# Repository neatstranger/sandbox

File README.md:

## Purpose
Just needed a place to document the build.

## Overview
- Clock
- Registers
- Arithmetic Logic unit
- Random Access Memory
- Program Counter
- Output Register

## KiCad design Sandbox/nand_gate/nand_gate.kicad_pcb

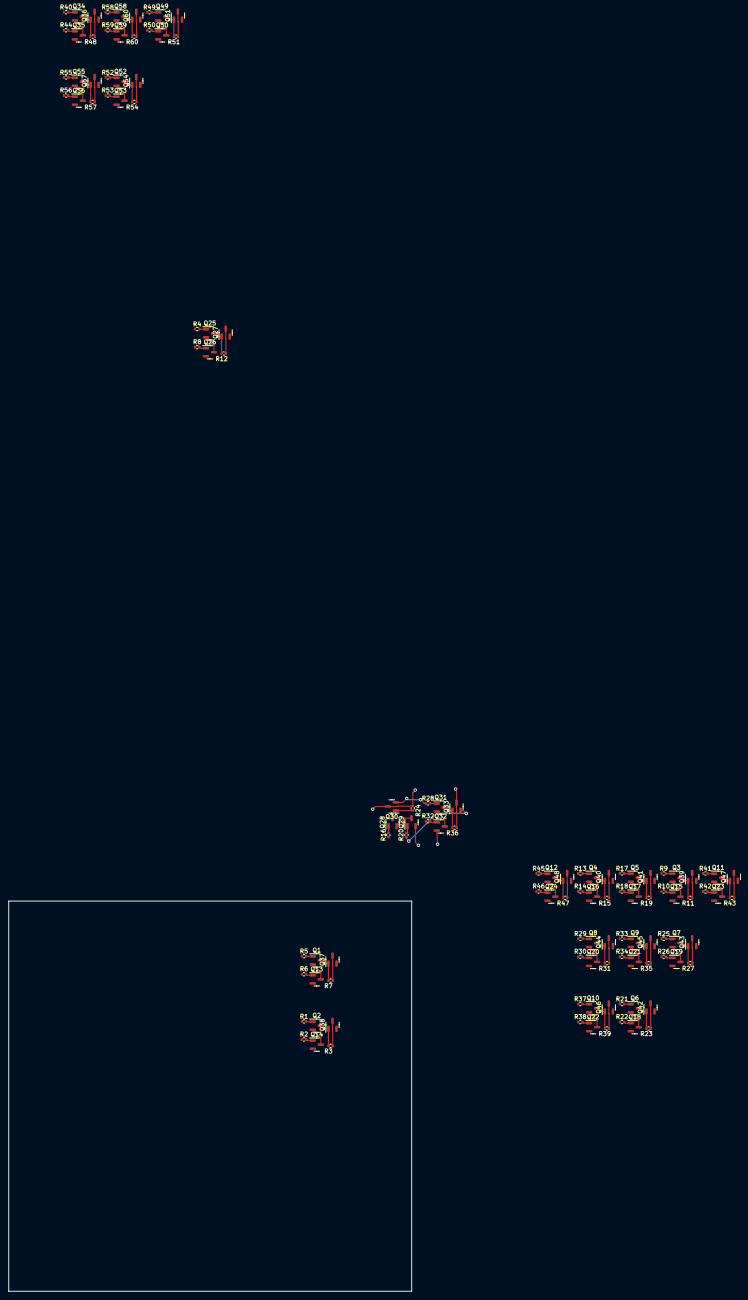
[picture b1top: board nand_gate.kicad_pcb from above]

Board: 4 copper layers, 94.8 x 91.8 mm, 120 parts (0 on the bottom side), 105 nets.

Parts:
Q1, Q2, Q3, Q4, Q5, Q6, Q7, Q8, Q9, Q10, Q11, Q12, Q13, Q14, Q15, Q16, Q17, Q18, Q19, Q20, Q21, Q22, Q23, Q24, Q25, Q26, Q27, Q28, Q29, Q30, Q31, Q32, Q33, Q34, Q35, Q36, Q37, Q38, Q39, Q40, Q41, Q42, Q43, Q44, Q45, Q46, Q47, Q48, Q49, Q50, Q51, Q52, Q53, Q54, Q55, Q56, Q57, Q58, Q59, Q60: Q_NPN_BEC; SOT-23
R1, R2, R3, R4, R5, R6, R7, R8, R9, R10, R11, R12, R13, R14, R15, R16, R17, R18, R19, R20, R21, R22, R23, R24, R25, R26, R27, R28, R29, R30, R31, R32, R33, R34, R35, R36, R37, R38, R39, R40, R41, R42, R43, R44, R45, R46, R47, R48, R49, R50, R51, R52, R53, R54, R55, R56, R57, R58, R59, R60: 1k; R_0402_1005Metric

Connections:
/D-Flip Flop/!Q: Q46.2 (E), R30.1
/D-Flip Flop/Clock: R41.1, R42.1
/D-Flip Flop/D-Latch1/Enable: Q48.2 (E), R26.1, R33.1
/D-Flip Flop/D-Latch1/SR-Latch/Reset: Q45.2 (E), R38.1
/D-Flip Flop/D-Latch1/SR-Latch/Set: Q43.2 (E), R29.1
/D-Flip Flop/D-Latch1/nand_gate3/B: Q42.2 (E), R34.1
/D-Flip Flop/D-Latch/!Q: Q38.2 (E), R6.1
/D-Flip Flop/D-Latch/Enable: Q47.2 (E), R10.1, R13.1, R45.1, R46.1
/D-Flip Flop/D-Latch/Q: Q37.2 (E), R1.1, R21.1, R22.1, R25.1
/D-Flip Flop/D-Latch/SR-Latch/Reset: Q40.2 (E), R2.1
/D-Flip Flop/D-Latch/SR-Latch/Set: Q39.2 (E), R5.1
/D-Flip Flop/D-Latch/nand_gate3/B: Q41.2 (E), R14.1
/D-Flip Flop/Data: R9.1, R17.1, R18.1
/D-Flip Flop/Q: Q44.2 (E), R37.1
/D-Latch2/!Q: Q57.2 (E), R44.1
/D-Latch2/Data: R49.1, R50.1, R52.1
/D-Latch2/Enable: R53.1, R58.1
/D-Latch2/Q: Q36.2 (E), R55.1
/D-Latch2/SR-Latch/Reset: Q60.2 (E), R56.1
/D-Latch2/SR-Latch/Set: Q54.2 (E), R40.1
/D-Latch2/nand_gate3/B: Q51.2 (E), R59.1
/SR-Latch1/!Q: Q33.2 (E), R20.1
/SR-Latch1/Q: Q30.2 (E), R28.1
GND: Q13.2 (E), Q14.2 (E), Q15.2 (E), Q16.2 (E), Q17.2 (E), Q18.2 (E), Q19.2 (E), Q20.2 (E), Q21.2 (E), Q22.2 (E), Q23.2 (E), Q24.2 (E), Q26.2 (E), Q29.2 (E), Q32.2 (E), Q35.2 (E), Q50.2 (E), Q53.2 (E), Q56.2 (E), Q59.2 (E)
unnamed: Q1.1 (B), R5.2
unnamed: Q1.3 (C), Q37.1 (B), R7.1
unnamed: Q1.2 (E), Q13.3 (C)
unnamed: Q2.1 (B), R1.2
unnamed: Q2.3 (C), Q38.1 (B), R3.1
unnamed: Q3.1 (B), R9.2
unnamed: Q3.3 (C), Q39.1 (B), R11.1
unnamed: Q4.1 (B), R13.2
unnamed: Q4.3 (C), Q40.1 (B), R15.1
unnamed: Q5.1 (B), R17.2
unnamed: Q6.1 (B), R21.2
unnamed: Q7.1 (B), R25.2
unnamed: Q8.1 (B), R29.2
unnamed: Q9.1 (B), R33.2
unnamed: Q10.1 (B), R37.2
unnamed: Q10.3 (C), Q46.1 (B), R39.1
unnamed: Q10.2 (E), Q22.3 (C)
unnamed: Q11.1 (B), R41.2
unnamed: Q11.3 (C), Q47.1 (B), R43.1
unnamed: Q11.2 (E), Q23.3 (C)
unnamed: Q12.1 (B), R45.2
unnamed: Q12.3 (C), Q48.1 (B), R47.1
unnamed: Q12.2 (E), Q24.3 (C)
unnamed: Q13.1 (B), R6.2
unnamed: Q14.1 (B), R2.2
unnamed: Q2.2 (E), Q14.3 (C)
unnamed: Q15.1 (B), R10.2
unnamed: Q3.2 (E), Q15.3 (C)
unnamed: Q16.1 (B), R14.2
unnamed: Q4.2 (E), Q16.3 (C)
unnamed: Q17.1 (B), R18.2
unnamed: Q5.2 (E), Q17.3 (C)
unnamed: Q18.1 (B), R22.2
unnamed: Q6.2 (E), Q18.3 (C)
unnamed: Q19.1 (B), R26.2
unnamed: Q7.2 (E), Q19.3 (C)
unnamed: Q20.1 (B), R30.2
unnamed: Q8.2 (E), Q20.3 (C)
unnamed: Q21.1 (B), R34.2
unnamed: Q9.2 (E), Q21.3 (C)
unnamed: Q22.1 (B), R38.2
unnamed: Q23.1 (B), R42.2
unnamed: Q24.1 (B), R46.2
unnamed: Q25.1 (B), R4.2
unnamed: Q25.3 (C), Q27.1 (B), R12.1
unnamed: Q25.2 (E), Q26.3 (C)
unnamed: Q26.1 (B), R8.2
unnamed: Q28.1 (B), R16.2
unnamed: Q28.3 (C), Q30.1 (B), R24.1
unnamed: Q28.2 (E), Q29.3 (C)
unnamed: Q29.1 (B), R20.2
unnamed: Q31.1 (B), R28.2
unnamed: Q31.3 (C), Q33.1 (B), R36.1
unnamed: Q31.2 (E), Q32.3 (C)
unnamed: Q32.1 (B), R32.2
unnamed: Q34.1 (B), R40.2
unnamed: Q34.3 (C), Q36.1 (B), R48.1
unnamed: Q34.2 (E), Q35.3 (C)
unnamed: Q35.1 (B), R44.2
unnamed: Q5.3 (C), Q41.1 (B), R19.1
unnamed: Q6.3 (C), Q42.1 (B), R23.1
unnamed: Q7.3 (C), Q43.1 (B), R27.1
unnamed: Q8.3 (C), Q44.1 (B), R31.1
unnamed: Q9.3 (C), Q45.1 (B), R35.1
unnamed: Q49.1 (B), R49.2
unnamed: Q49.3 (C), Q51.1 (B), R51.1
unnamed: Q49.2 (E), Q50.3 (C)
unnamed: Q50.1 (B), R50.2
unnamed: Q52.1 (B), R52.2
unnamed: Q52.3 (C), Q54.1 (B), R54.1
unnamed: Q52.2 (E), Q53.3 (C)
unnamed: Q53.1 (B), R53.2
unnamed: Q55.1 (B), R55.2
unnamed: Q55.3 (C), Q57.1 (B), R57.1
unnamed: Q55.2 (E), Q56.3 (C)
unnamed: Q56.1 (B), R56.2
unnamed: Q58.1 (B), R58.2
unnamed: Q58.3 (C), Q60.1 (B), R60.1
unnamed: Q58.2 (E), Q59.3 (C)
unnamed: Q59.1 (B), R59.2
VCC: Q27.3 (C), Q30.3 (C), Q33.3 (C), Q36.3 (C), Q37.3 (C), Q38.3 (C), Q39.3 (C), Q40.3 (C), Q41.3 (C), Q42.3 (C), Q43.3 (C), Q44.3 (C), Q45.3 (C), Q46.3 (C), Q47.3 (C), Q48.3 (C), Q51.3 (C), Q54.3 (C), Q57.3 (C), Q60.3 (C), R3.2, R7.2, R11.2, R12.2, R15.2, R19.2, R23.2, R24.2, R27.2, R31.2, R35.2, R36.2, R39.2, R43.2, R47.2, R48.2, R51.2, R54.2, R57.2, R60.2

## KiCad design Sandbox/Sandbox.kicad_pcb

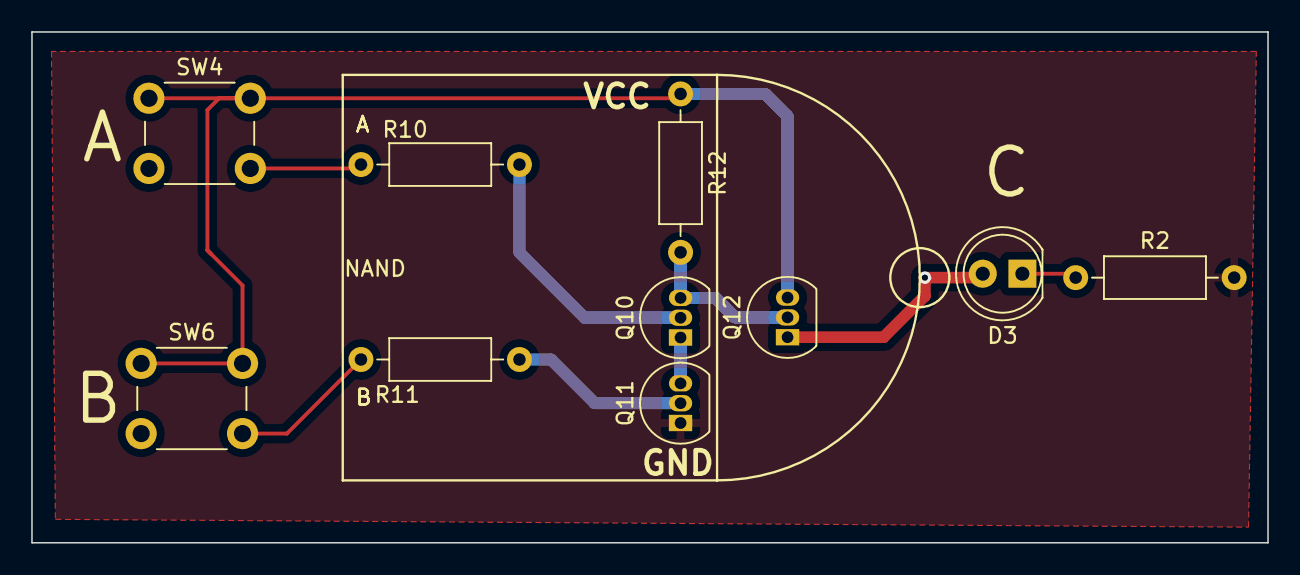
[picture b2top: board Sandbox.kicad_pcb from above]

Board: 2 copper layers, 79.2 x 32.8 mm, 10 parts (0 on the bottom side), 10 nets.

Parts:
D3: LED; LED_D5.0mm_Clear
Q10, Q11, Q12: 2N3904; TO-92_Inline
R2, R10, R11: 1000; R_Axial_DIN0207_L6.3mm_D2.5mm_P10.16mm_Horizontal
R12: 100; R_Axial_DIN0207_L6.3mm_D2.5mm_P10.16mm_Horizontal
SW4, SW6: SW_Push_Dual; SW_PUSH_6mm

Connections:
/Register/D-Flip-Flop/D-Latch1/SR-Latch/NAND11/A: R10.1, SW4.2
/Register/D-Flip-Flop/D-Latch1/SR-Latch/NAND11/B: R11.1, SW6.2
/Register/D-Flip-Flop/D-Latch1/SR-Latch/NAND11/C: D3.2 (A), Q12.1 (E)
GND: Q11.1 (E), R2.2
unnamed: D3.1 (K), R2.1
unnamed: Q10.2 (B), R10.2
unnamed: Q10.3 (C), Q12.2 (B), R12.2
unnamed: Q10.1 (E), Q11.3 (C)
unnamed: Q11.2 (B), R11.2
VCC: Q12.3 (C), R12.1, SW4.1, SW6.1

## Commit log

2023-12-22 Added Resource Section
2023-12-23 Just messing arround.
2023-12-23 Test D-Latch Finished
2023-12-25 Nand Gate
2023-12-25 Layout for nand gate
2023-12-25 Updating schematic
2023-12-25 D-Latch Done
2023-12-25 Added D Flip Flop
2023-12-29 Added Some stuff
2024-02-15 Moved Some Things Around
2024-02-20 Working
2024-02-20 woring on layout.
